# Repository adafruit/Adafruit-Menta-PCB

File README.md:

# Adafruit MENTA

These are the Eagle CAD files for the Adafruit MENTA

Introducing the MENTA, a portable minty Arduino-compatible project that fits into a common mint tin. We took our super popular Boarduino series, and wrapped it with a prototyping area into a rounded PCB that slots directly into an Altoids-sized metal tin. We included everything you expect to jump-start your project:

- DC power adapter jack with polarity protection
- Beefy 1 Amp 5V regulator and 250mA 3.3V regulator for 3.3V devices
- Green power LED, red blinky LED on pin 13
- ISP-6 standard reprogramming header
- FTDI interface plug to connect an [FTDI Friend](http://www.adafruit.com/products/284) or [FTDI Cable](https://www.adafruit.com/products/70)
- Female header set so you can plug standard Arduino-compatible shields in.
- There's four mounting holes if you want to attach it permanently to a box or plate
- Massive prototyping area so you can have the finished project all fit together in a protective box.
- Four rubber bumpers to protect your table from scratching, and the PCB and parts from the metal tin
- [MENTA sticker (unaffixed)](http://www.adafruit.com/products/873)
- __This pack even comes with the mint tin itself!__

Comes as a kit of parts, this is an excellent beginner project, with [step-by-step instructions](http://ladyada.net/make/menta/index.html) even for someone who has never soldered before. [A soldering iron, diagonal cutters and solder](https://www.adafruit.com/category/8) are required to complete the project. You'll also need an FTDI adapter such as the [FTDI Friend](http://www.adafruit.com/products/284) or [FTDI Cable](https://www.adafruit.com/products/70) to program it via the Arduino IDE.

### License

Adafruit invests time and resources providing this open source design, please support Adafruit and open-source hardware by purchasing products from [Adafruit](https://www.adafruit.com)!

Designed by Limor Fried/Ladyada for Adafruit Industries.

Creative Commons Attribution/Share-Alike, all text above must be included in any redistribution. See license.txt for additional details.

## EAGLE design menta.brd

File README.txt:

These are the Eagle CAD files for the Adafruit MENTA
  ----> http://www.ladyada.net/make/menta
 
Check out the link above for our tutorials and wiring diagrams.

Adafruit invests time and resources providing this open source code,
please support Adafruit and open-source hardware by purchasing
products from Adafruit!

Designed by Limor Fried/Ladyada for Adafruit Industries.
Creative Commons Attribution/Share-Alike, all text above must be included in any redistribution

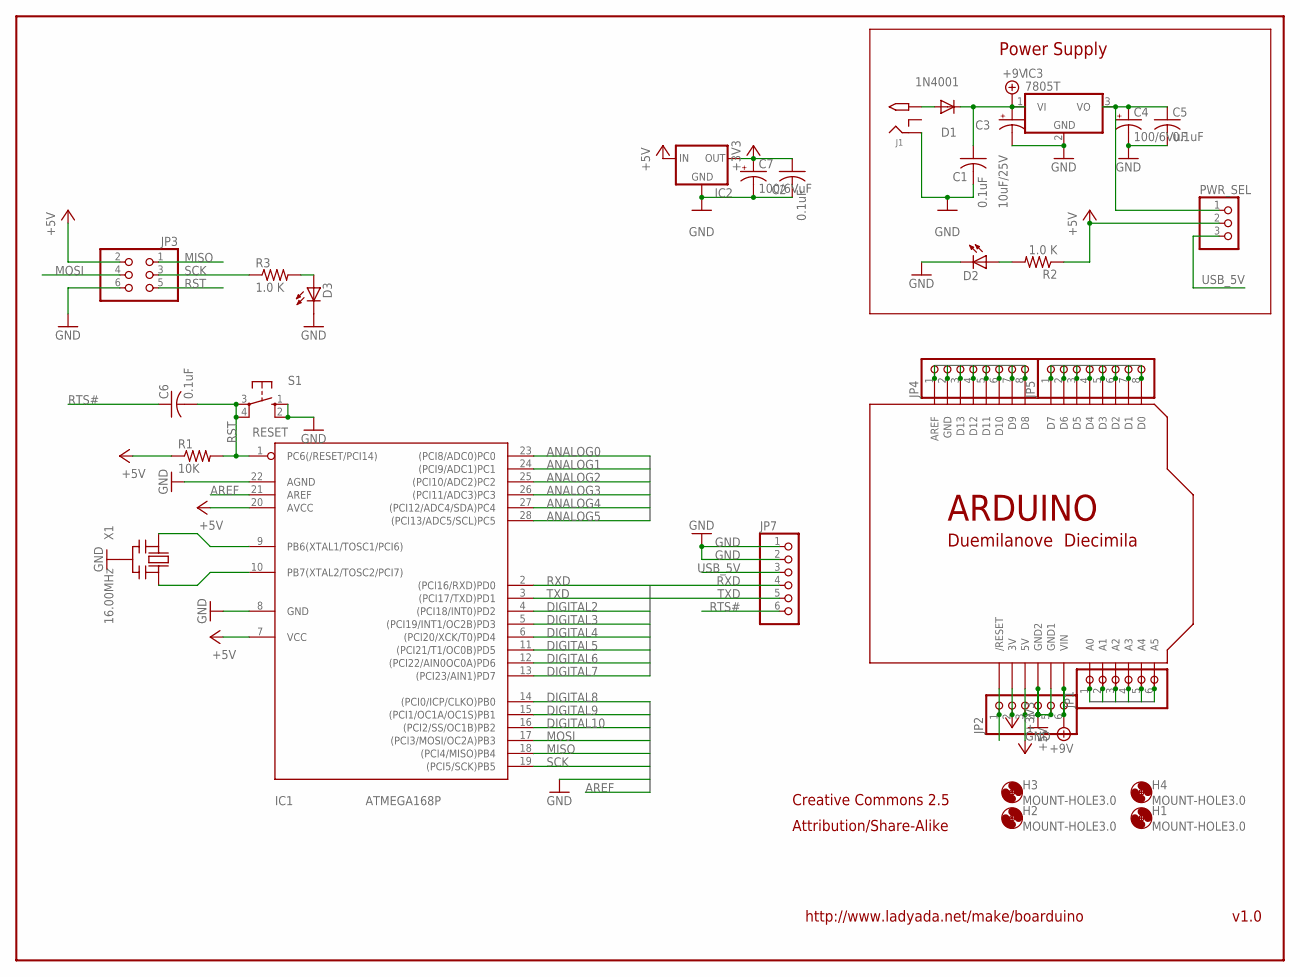
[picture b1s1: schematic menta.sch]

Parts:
C1, C2, C5, C6: 0.1uF; C025-025X050
C3: 10uF/25V; E2,5-6
C4, C7: 100/6VuF; E2,5-6
D1: 1N4001; DO41-10
D2: LED3MM
D3: Green; LED3MM
H1, H2, H3, H4: MOUNT-HOLE3.0; 3,0
IC1: ATMEGA168P; DIL28/3
IC2: MCP1700INLINE; TO92-INLINE
IC3: 7805T; TO220H
J1: 2.1MMJACK; PJ-102A
JP1, JP2: PINHD-1X6CB; 1X06-CLEANBIG
JP3: PINHD-2X3; 2X03
JP4, JP5: PINHD-1X8CLEANBIG; 1X08-CLEANBIG
JP7: PINHD-1X6CLEAN; 1X06-CLEAN
PWR_SEL: PINHD-1X3; 1X03
R1: 10K; 0207/10
R2, R3: 1.0 K; 0207/10
S1: RESET; B3F-10XX
U$2: ARDUINO-NOHOLE
X1: 16.00MHz; CERM_OSC

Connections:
+3V3: C2.1, C7.+, IC2.3 (OUT), JP2.2, U$2.3V
+5V: IC1.7 (VCC), IC1.20 (AVCC), IC2.2 (IN), JP2.3, JP3.2, PWR_SEL.2, R1.1, R2.1, U$2.5V
+9V: C1.1, C3.+, D1.C, IC3.1 (VI), JP2.6, U$2.VIN
ANALOG0: IC1.23 ((PCI8/ADC0)PC0), JP1.1, U$2.A0
ANALOG1: IC1.24 ((PCI9/ADC1)PC1), JP1.2, U$2.A1
ANALOG2: IC1.25 ((PCI10/ADC2)PC2), JP1.3, U$2.A2
ANALOG3: IC1.26 ((PCI11/ADC3)PC3), JP1.4, U$2.A3
ANALOG4: IC1.27 ((PCI12/ADC4/SDA)PC4), JP1.5, U$2.A4
ANALOG5: IC1.28 ((PCI13/ADC5/SCL)PC5), JP1.6, U$2.A5
AREF: IC1.21 (AREF), JP4.1, U$2.AREF
DIGITAL2: IC1.4 ((PCI18/INT0)PD2), JP5.6, U$2.D2
DIGITAL3: IC1.5 ((PCI19/INT1/OC2B)PD3), JP5.5, U$2.D3
DIGITAL4: IC1.6 ((PCI20/XCK/T0)PD4), JP5.4, U$2.D4
DIGITAL5: IC1.11 ((PCI21/T1/OC0B)PD5), JP5.3, U$2.D5
DIGITAL6: IC1.12 ((PCI22/AIN0OC0A)PD6), JP5.2, U$2.D6
DIGITAL7: IC1.13 ((PCI23/AIN1)PD7), JP5.1, U$2.D7
DIGITAL8: IC1.14 ((PCI0/ICP/CLKO)PB0), JP4.8, U$2.D8
DIGITAL9: IC1.15 ((PCI1/OC1A/OC1S)PB1), JP4.7, U$2.D9
DIGITAL10: IC1.16 ((PCI2/SS/OC1B)PB2), JP4.6, U$2.D10
GND: C1.2, C2.2, C3.-, C4.-, C5.2, C7.-, D2.K (C), D3.K (C), IC1.8 (GND), IC1.22 (AGND), IC2.1 (GND), IC3.2 (GND), J1.RING, JP2.4, JP2.5, JP3.6, JP4.2, JP7.1, JP7.2, S1.1 (S), S1.2 (S1), U$2.GND, U$2.GND1, U$2.GND2, X1.P$2 (GND)
MISO: IC1.18 ((PCI4/MISO)PB4), JP3.1, JP4.4, U$2.D12
MOSI: IC1.17 ((PCI3/MOSI/OC2A)PB3), JP3.4, JP4.5, U$2.D11
unnamed: IC1.9 (PB6(XTAL1/TOSC1/PCI6)), X1.P$1 (IN)
unnamed: IC1.10 (PB7(XTAL2/TOSC2/PCI7)), X1.P$3 (OUT)
unnamed: D2.A, R2.2
unnamed: D3.A, R3.2
unnamed: C4.+, C5.1, IC3.3 (VO), PWR_SEL.1
unnamed: D1.A, J1.TIP
RST: C6.2, IC1.1 (PC6(/RESET/PCI14)), JP2.1, JP3.5, R1.2, S1.3, S1.4 (P1), U$2.RESET (/RESET)
RTS#: C6.1, JP7.6
RXD: IC1.2 ((PCI16/RXD)PD0), JP5.8, JP7.4, U$2.D0
SCK: IC1.19 ((PCI5/SCK)PB5), JP3.3, JP4.3, R3.1, U$2.D13
TXD: IC1.3 ((PCI17/TXD)PD1), JP5.7, JP7.5, U$2.D1
USB_5V: JP7.3, PWR_SEL.3

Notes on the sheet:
Power Supply
v1.0
http://www.ladyada.net/make/boarduino
Creative Commons 2.5
Attribution/Share-Alike

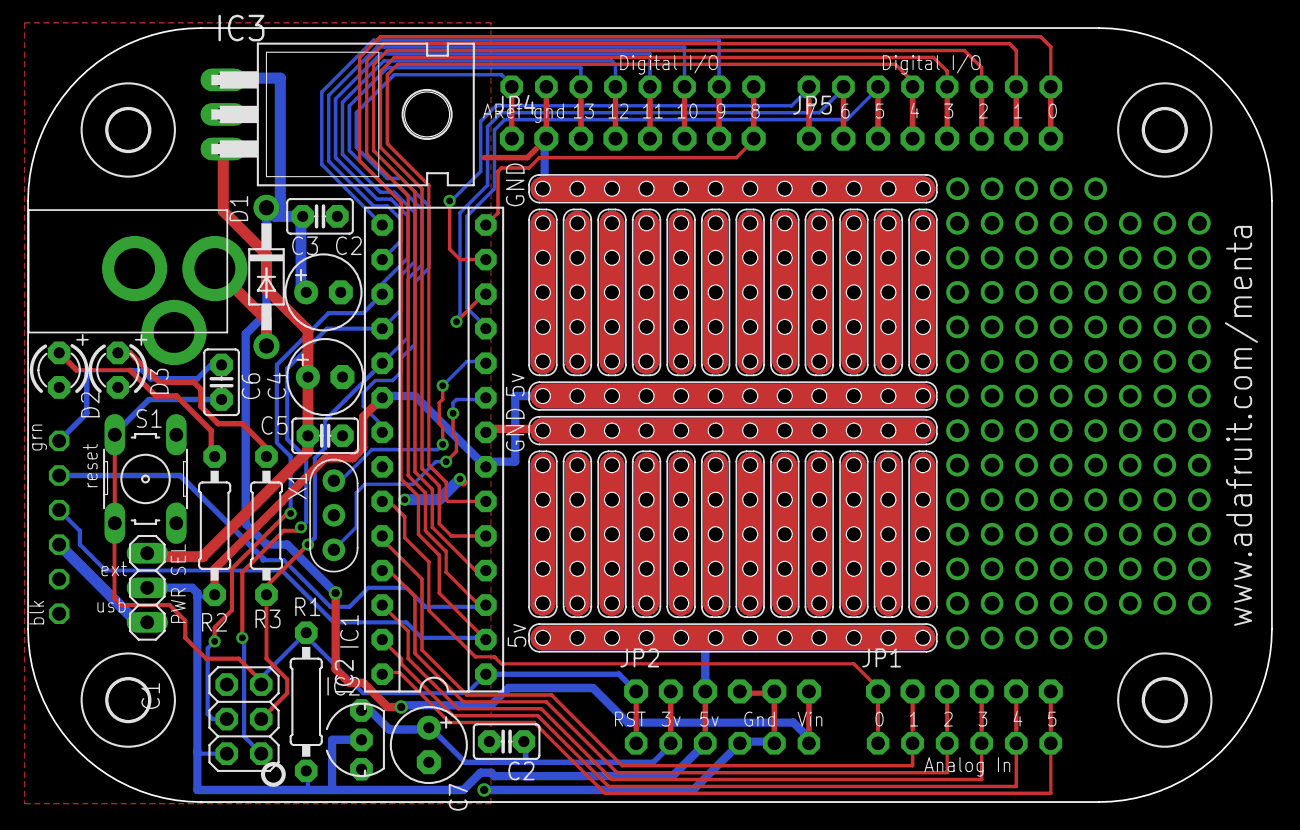
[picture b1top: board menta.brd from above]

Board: 2 copper layers, 91.4 x 56.9 mm, 60 parts (1 on the bottom side), 34 nets.

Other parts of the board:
U$3, U$4, U$5, U$6: 12-STRIP
U$7, U$8, U$9, U$10, U$11, U$12, U$13, U$14, U$15, U$16, U$17, U$18, U$19, U$20, U$21, U$22, U$23, U$24, U$25, U$26, U$27, U$28, U$29, U$30: 5-STRIP
U$31: ALTOIDSTIN-DIM

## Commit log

2012-04-20 read
2019-04-03 image + readme
2019-04-04 Revert "Update README.md"
    This reverts commit 369cb76f6509e43673b52bfb06ec66a29c2916ba.
2019-04-04 readme fix
2026-06-03 update file format to XML
